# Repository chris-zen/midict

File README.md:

# midict
Hardware, firmware and software for my home made MIDI controllers

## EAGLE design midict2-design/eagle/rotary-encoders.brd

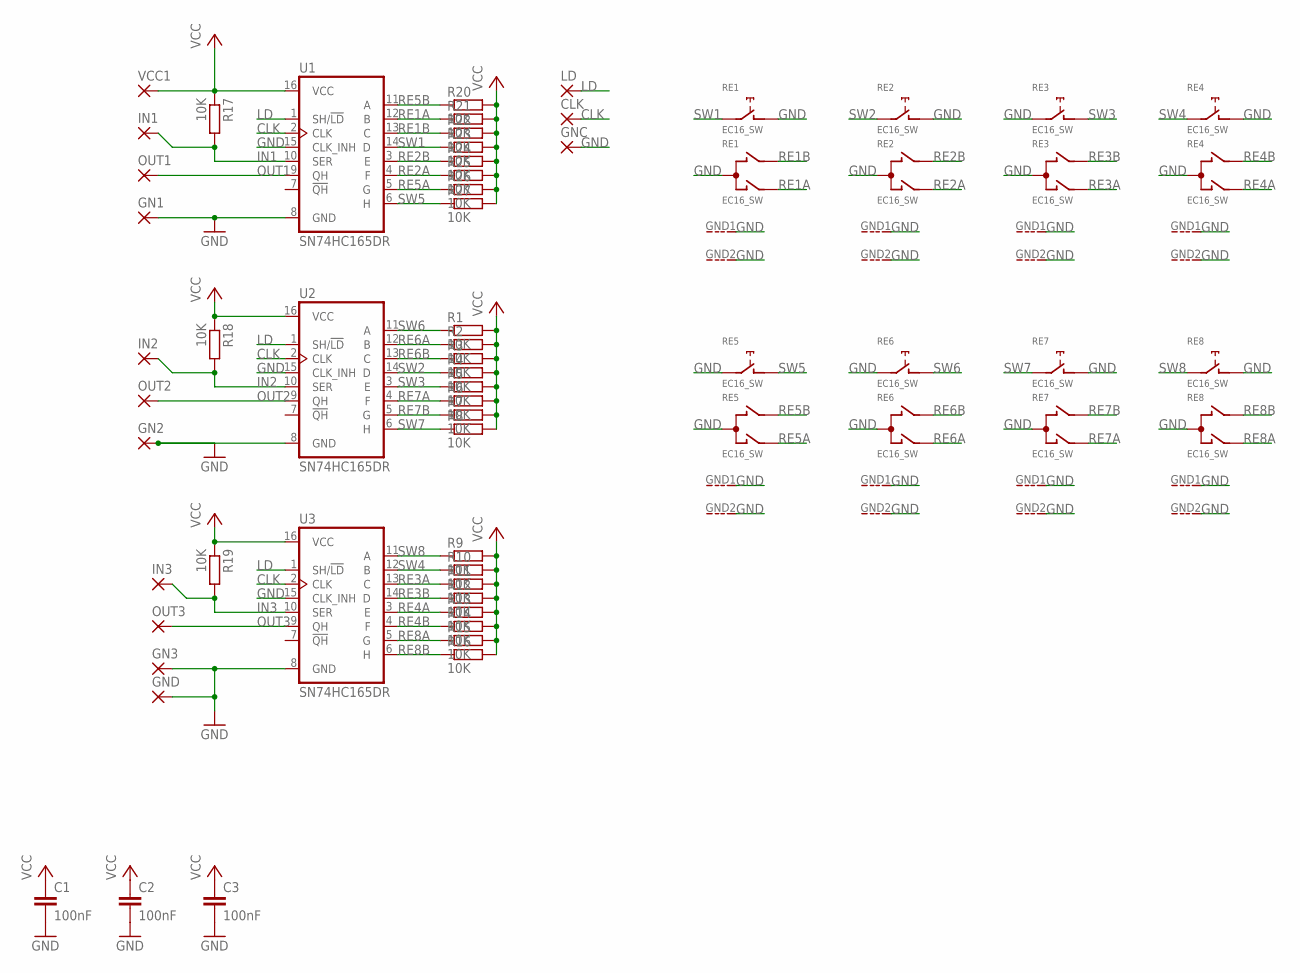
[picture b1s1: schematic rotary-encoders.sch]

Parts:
C1, C2, C3: 100nF; C0805
CLK: 1,6/0,9
GN1, GN2, GN3: 1,6/0,9
GNC: 1,6/0,9
GND: 1,6/0,9
IN1, IN2, IN3: 1,6/0,9
LD: 1,6/0,9
OUT1, OUT2, OUT3: 1,6/0,9
R1, R2, R3, R4, R5, R6, R7, R8, R9, R10, R11, R12, R13, R14, R15, R16, R17, R18, R19, R20, R21, R22, R23, R24, R25, R26, R27: 10K; R0805
RE1, RE2, RE3, RE4, RE5, RE6, RE7, RE8: EC16_SW
U1, U2, U3: SN74HC165DR; SO16
VCC1: 1,6/0,9

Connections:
CLK: CLK.1, U1.2 (CLK), U2.2 (CLK), U3.2 (CLK)
GND: C1.2, C2.2, C3.2, GN1.1, GN2.1, GN3.1, GNC.1, GND.1, RE1.C, RE1.D (1), RE1.GND1 (G), RE1.GND2 (G), RE2.C, RE2.D (1), RE2.GND1 (G), RE2.GND2 (G), RE3.C, RE3.E (2), RE3.GND1 (G), RE3.GND2 (G), RE4.C, RE4.D (1), RE4.GND1 (G), RE4.GND2 (G), RE5.C, RE5.E (2), RE5.GND1 (G), RE5.GND2 (G), RE6.C, RE6.E (2), RE6.GND1 (G), RE6.GND2 (G), RE7.C, RE7.D (1), RE7.GND1 (G), RE7.GND2 (G), RE8.C, RE8.D (1), RE8.GND1 (G), RE8.GND2 (G), U1.8 (GND), U1.15 (CLK_INH), U2.8 (GND), U2.15 (CLK_INH), U3.8 (GND), U3.15 (CLK_INH)
IN1: IN1.1, R17.2, U1.10 (SER)
IN2: IN2.1, R18.2, U2.10 (SER)
IN3: IN3.1, R19.2, U3.10 (SER)
LD: LD.1, U1.1 (SH/!LD), U2.1 (SH/!LD), U3.1 (SH/!LD)
OUT1: OUT1.1, U1.9 (QH)
OUT2: OUT2.1, U2.9 (QH)
OUT3: OUT3.1, U3.9 (QH)
RE1A: R21.1, RE1.A, U1.12 (B)
RE1B: R22.1, RE1.B, U1.13 (C)
RE2A: R25.1, RE2.A, U1.4 (F)
RE2B: R24.1, RE2.B, U1.3 (E)
RE3A: R11.1, RE3.A, U3.13 (C)
RE3B: R12.1, RE3.B, U3.14 (D)
RE4A: R13.1, RE4.A, U3.3 (E)
RE4B: R14.1, RE4.B, U3.4 (F)
RE5A: R26.1, RE5.A, U1.5 (G)
RE5B: R20.1, RE5.B, U1.11 (A)
RE6A: R2.1, RE6.A, U2.12 (B)
RE6B: R3.1, RE6.B, U2.13 (C)
RE7A: R6.1, RE7.A, U2.4 (F)
RE7B: R7.1, RE7.B, U2.5 (G)
RE8A: R15.1, RE8.A, U3.5 (G)
RE8B: R16.1, RE8.B, U3.6 (H)
SW1: R23.1, RE1.E (2), U1.14 (D)
SW2: R4.1, RE2.E (2), U2.14 (D)
SW3: R5.1, RE3.D (1), U2.3 (E)
SW4: R10.1, RE4.E (2), U3.12 (B)
SW5: R27.1, RE5.D (1), U1.6 (H)
SW6: R1.1, RE6.D (1), U2.11 (A)
SW7: R8.1, RE7.E (2), U2.6 (H)
SW8: R9.1, RE8.E (2), U3.11 (A)
VCC: C1.1, C2.1, C3.1, R1.2, R2.2, R3.2, R4.2, R5.2, R6.2, R7.2, R8.2, R9.2, R10.2, R11.2, R12.2, R13.2, R14.2, R15.2, R16.2, R17.1, R18.1, R19.1, R20.2, R21.2, R22.2, R23.2, R24.2, R25.2, R26.2, R27.2, U1.16 (VCC), U2.16 (VCC), U3.16 (VCC), VCC1.1

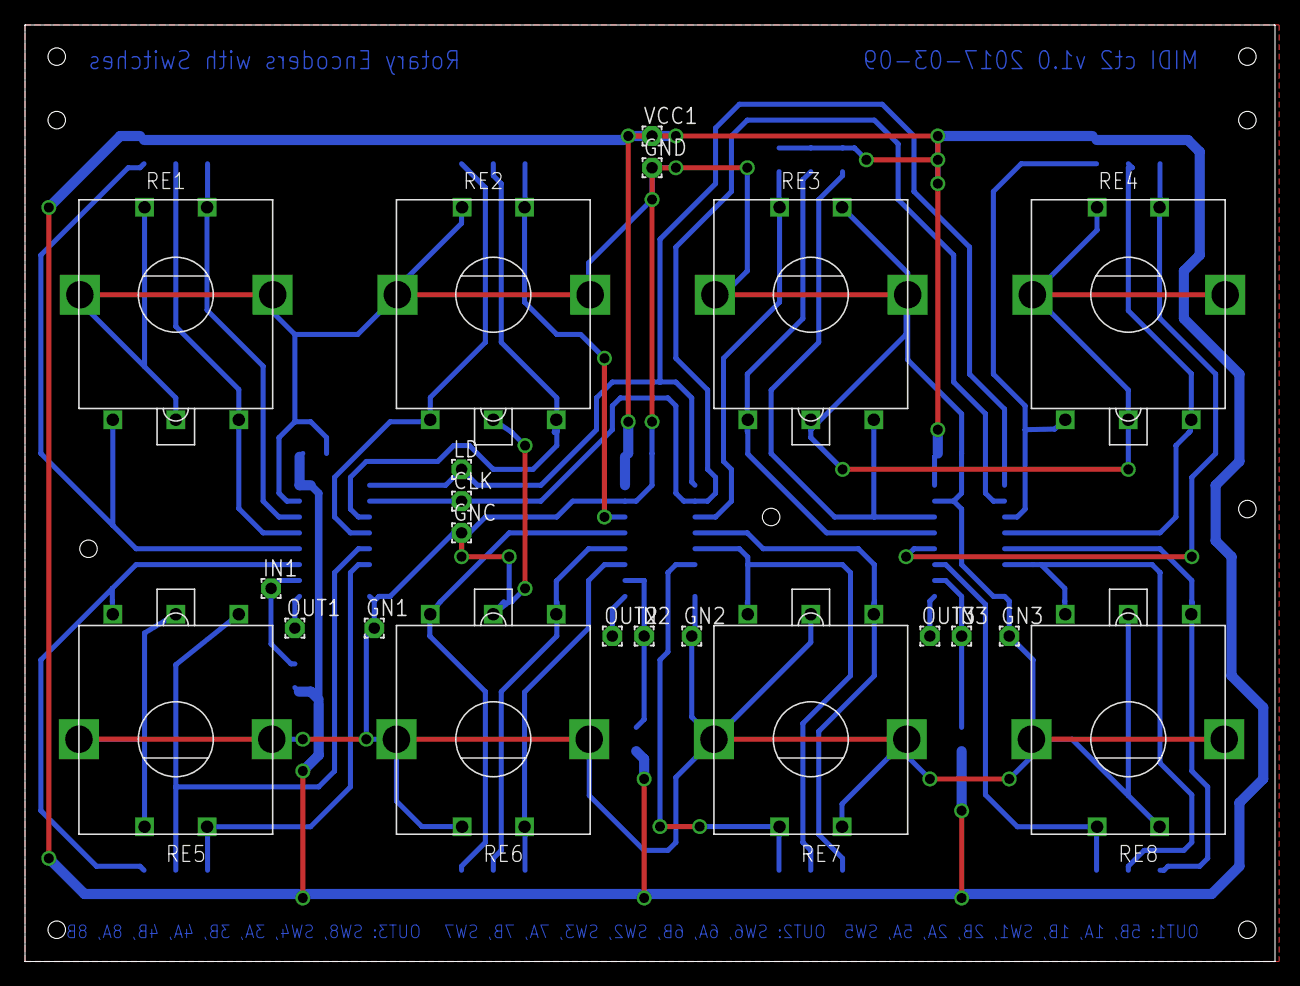
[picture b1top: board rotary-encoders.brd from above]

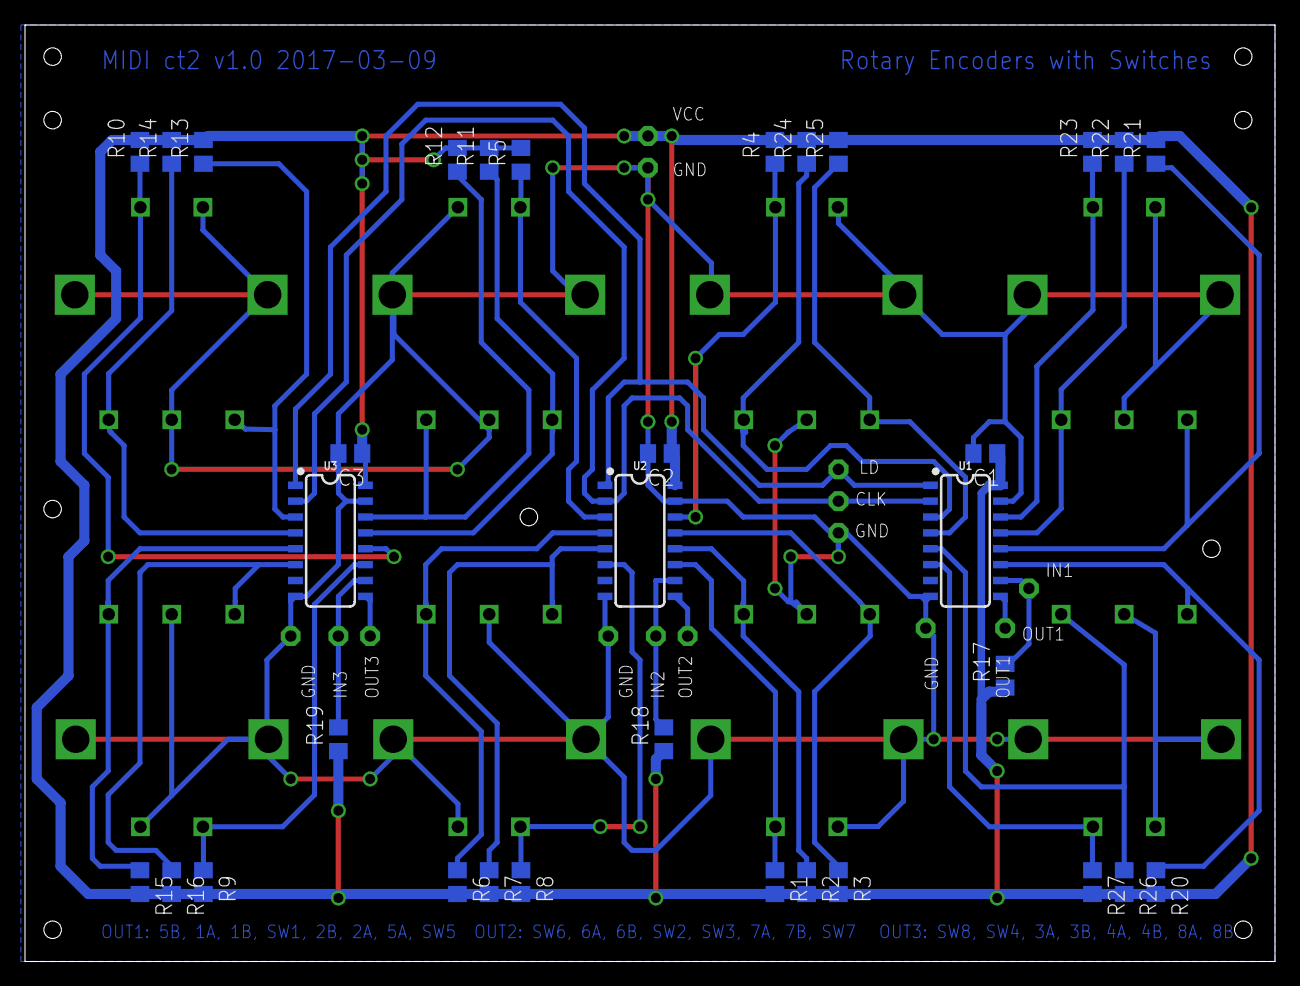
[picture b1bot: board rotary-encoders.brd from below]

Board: 2 copper layers, 100.0 x 74.9 mm, 55 parts (33 on the bottom side), 34 nets.

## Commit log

2016-12-12 Initial ESP prototype
2016-12-12 Added initial work on the software side
2017-03-09 Eagle design and initial firmware prototype
2017-04-09 midict2 rotary encoders build and verified
2022-11-08 Update info

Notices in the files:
parts and their libraries:
SparkFun-IC-Logic: Licensing: Creative Commons ShareAlike 4.0 International - https://creativecommons.org/licenses/by-sa/4.0
